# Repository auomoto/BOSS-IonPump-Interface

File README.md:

# BOSS-IonPump-Interface
The BOSS CCD dewars use a Modion C-1765V 2l/s ion pump with a custom vacuum fitting. This model number is not on the current modionvacuum.com website but the C-1765M looks similar.
The power supply is a Modion C-1766Q, which supplies the high voltage and also presents an analog signal indicating internal current that can be used as a vacuum pressure measurement. This power supply has an unusual 5-pin connector with a wall plug-in supply to supply power and also break out the signals.
To distribute the signals to the BOSS motion controller system (specMech) we use an interface box that supplies isolated 15 V to the two ion pumps (one on each of the two dewars) and conditions the analog signal for transmission to the control system.
[Link to the interface board description](https://docs.google.com/document/d/1ESppHA3kPF6aFfvCehlsRecCQ0mpgMWIIbT9OZ6ddFA/edit#)

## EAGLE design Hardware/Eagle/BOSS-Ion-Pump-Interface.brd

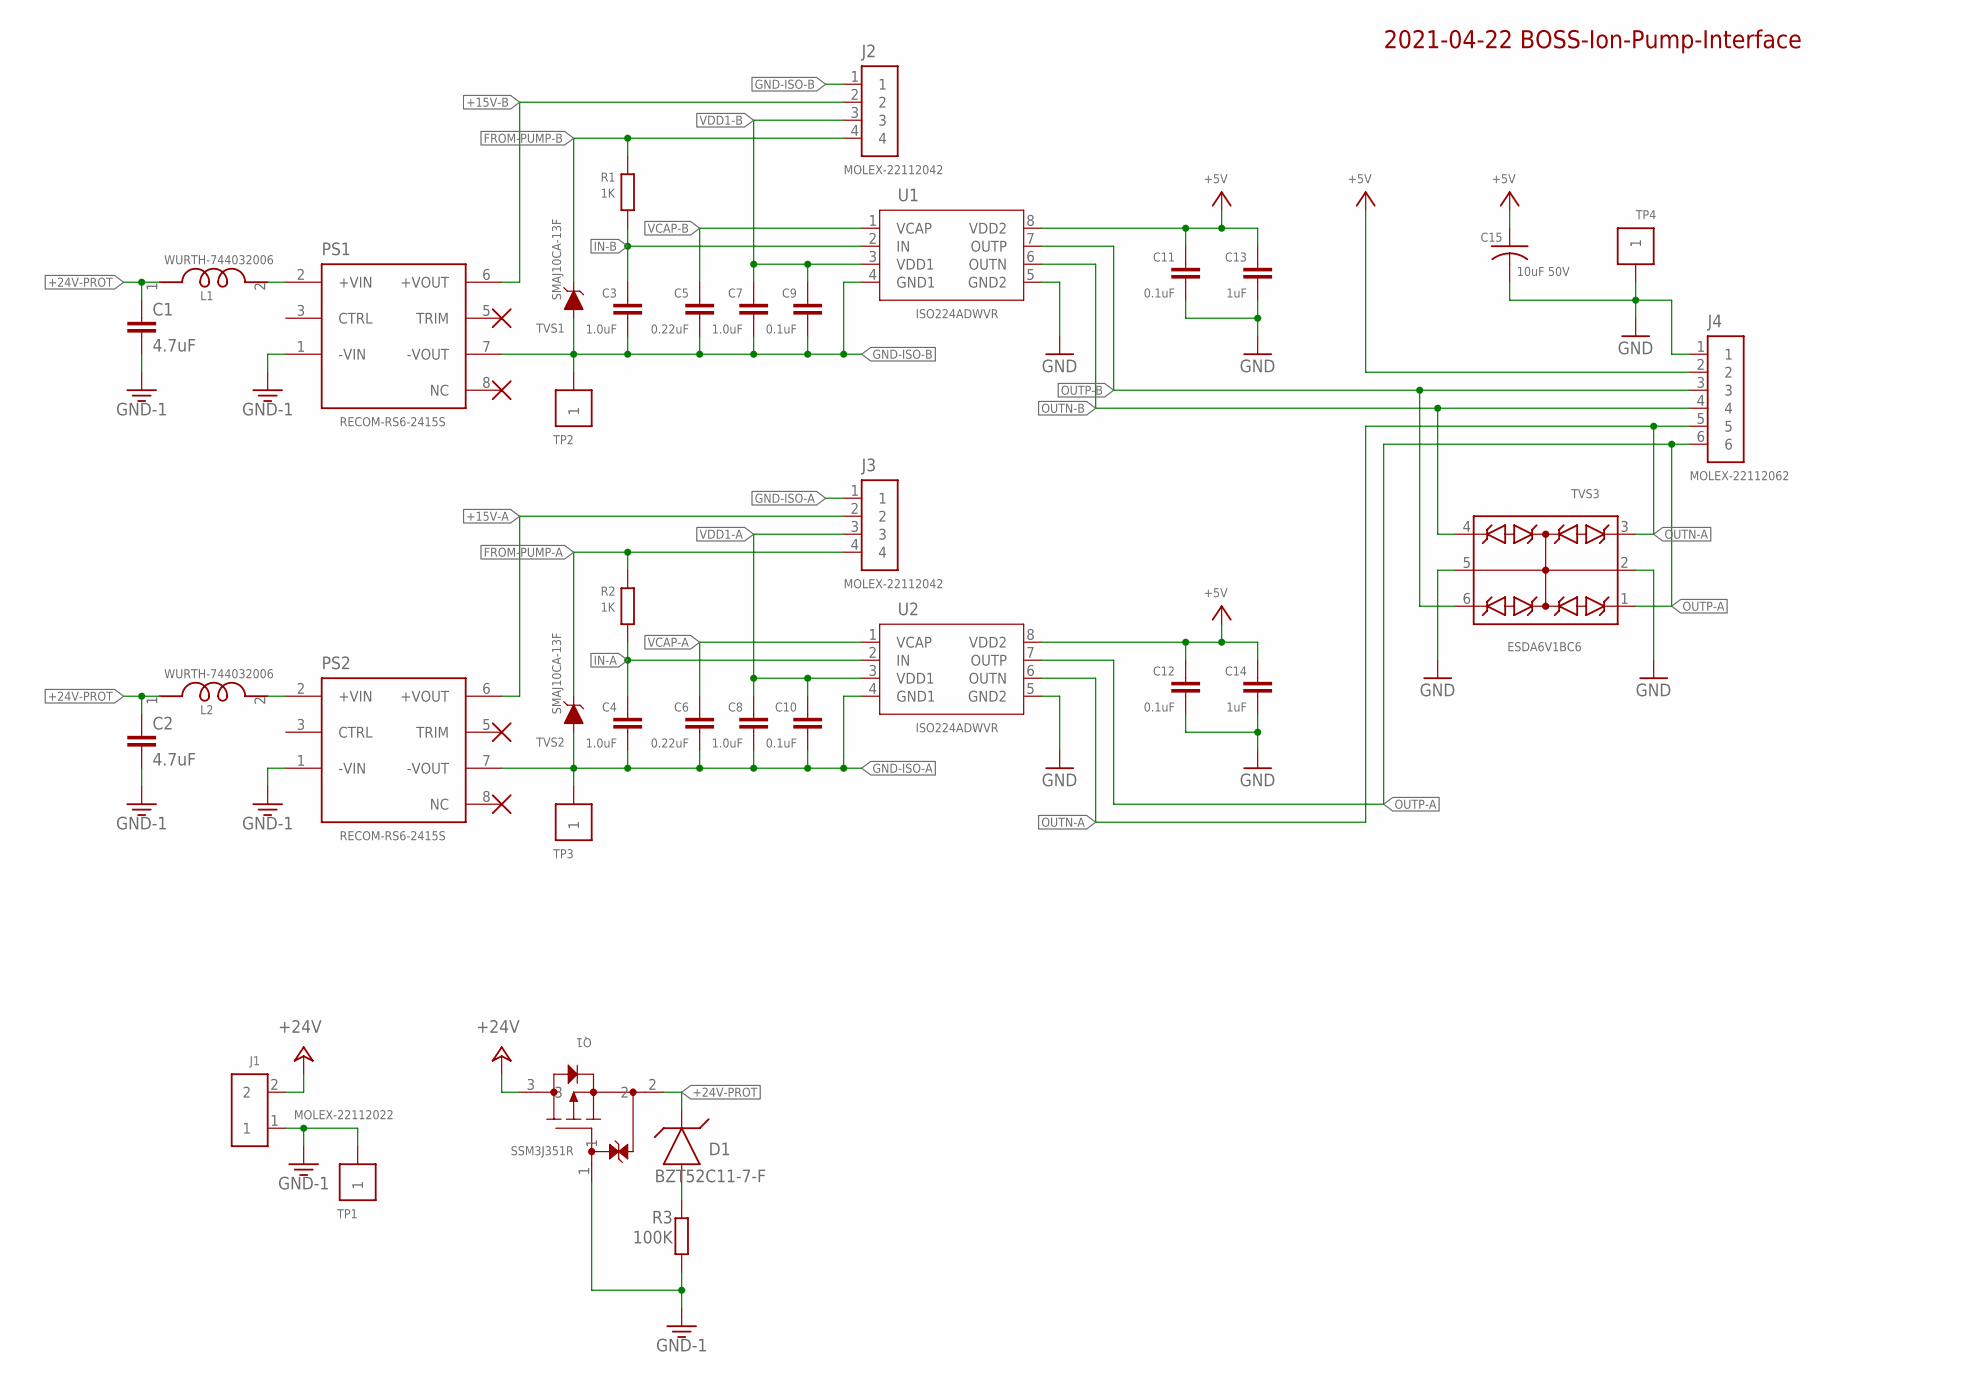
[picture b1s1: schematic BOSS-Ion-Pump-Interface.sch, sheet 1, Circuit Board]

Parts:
C1, C2: 4.7uF; C1206
C3, C4: 1.0uF; C0805
C5, C6: 0.22uF; C1206
C7, C8: 1.0uF; C1206
C9, C10: 0.1uF; C1206
C11, C12: 0.1uF; C0805
C13, C14: 1uF; C0805
C15: 10uF 50V; C1210
D1: BZT52C11-7-F; SOD123_DIO
J1: MOLEX-22112022; 1X02-MOLEX-22112022
J2, J3: MOLEX-22112042; 1X04-MOLEX-22112042
J4: MOLEX-22112062; 1X06-MOLEX-22112062
L1, L2: WURTH-744032006; WURTH-1210-INDUCTOR
PS1, PS2: RECOM-RS6-2415S; CONV_RS6-2415S
Q1: SSM3J351R; SOT-23F_TOS
R1, R2: 1K; R0805
R3: 100K; R0805
TP1, TP2, TP3, TP4: TP5000-TESTPOINT-BLK
TVS1, TVS2: SMAJ10CA-13F; SMA_DIO-M
TVS3: ESDA6V1BC6; SOT95P280X145-6N
U1, U2: ISO224ADWVR; DWV8_TEX

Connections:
+5V: C11.1, C12.1, C13.1, C14.1, C15.1, J4.2, U1.8 (VDD2), U2.8 (VDD2)
+15V-A: J3.2, PS2.6 (+VOUT)
+15V-B: J2.2, PS1.6 (+VOUT)
+24V: J1.2, Q1.3
+24V-PROT: C1.1, C2.1, D1.1 (C), L1.1, L2.1, Q1.2
+VIN-A: L2.2, PS2.2 (+VIN)
+VIN-B: L1.2, PS1.2 (+VIN)
FROM-PUMP-A: J3.4, R2.1, TVS2.1 (C)
FROM-PUMP-B: J2.4, R1.1, TVS1.1 (C)
GND: C11.2, C12.2, C13.2, C14.2, C15.2, J4.1, TP4.P$1, TVS3.2 (CC1), TVS3.5 (CC2), U1.5 (GND2), U2.5 (GND2)
GND-1: C1.2, C2.2, J1.1, PS1.1 (-VIN), PS2.1 (-VIN), Q1.1, R3.1, TP1.P$1
GND-ISO-A: C4.2, C6.2, C8.2, C10.2, J3.1, PS2.7 (-VOUT), TP3.P$1, TVS2.2 (A), U2.4 (GND1)
GND-ISO-B: C3.2, C5.2, C7.2, C9.2, J2.1, PS1.7 (-VOUT), TP2.P$1, TVS1.2 (A), U1.4 (GND1)
IN-A: C4.1, R2.2, U2.2 (IN)
IN-B: C3.1, R1.2, U1.2 (IN)
OUTN-A: J4.5, TVS3.3 (C2), U2.6 (OUTN)
OUTN-B: J4.4, TVS3.4 (C3), U1.6 (OUTN)
OUTP-A: J4.6, TVS3.1 (C1), U2.7 (OUTP)
OUTP-B: J4.3, TVS3.6 (C4), U1.7 (OUTP)
REVERSE-POL-ZENER: D1.2 (A), R3.2
VCAP-A: C6.1, U2.1 (VCAP)
VCAP-B: C5.1, U1.1 (VCAP)
VDD1-A: C8.1, C10.1, J3.3, U2.3 (VDD1)
VDD1-B: C7.1, C9.1, J2.3, U1.3 (VDD1)

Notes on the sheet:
2021-04-22 BOSS-Ion-Pump-Interface

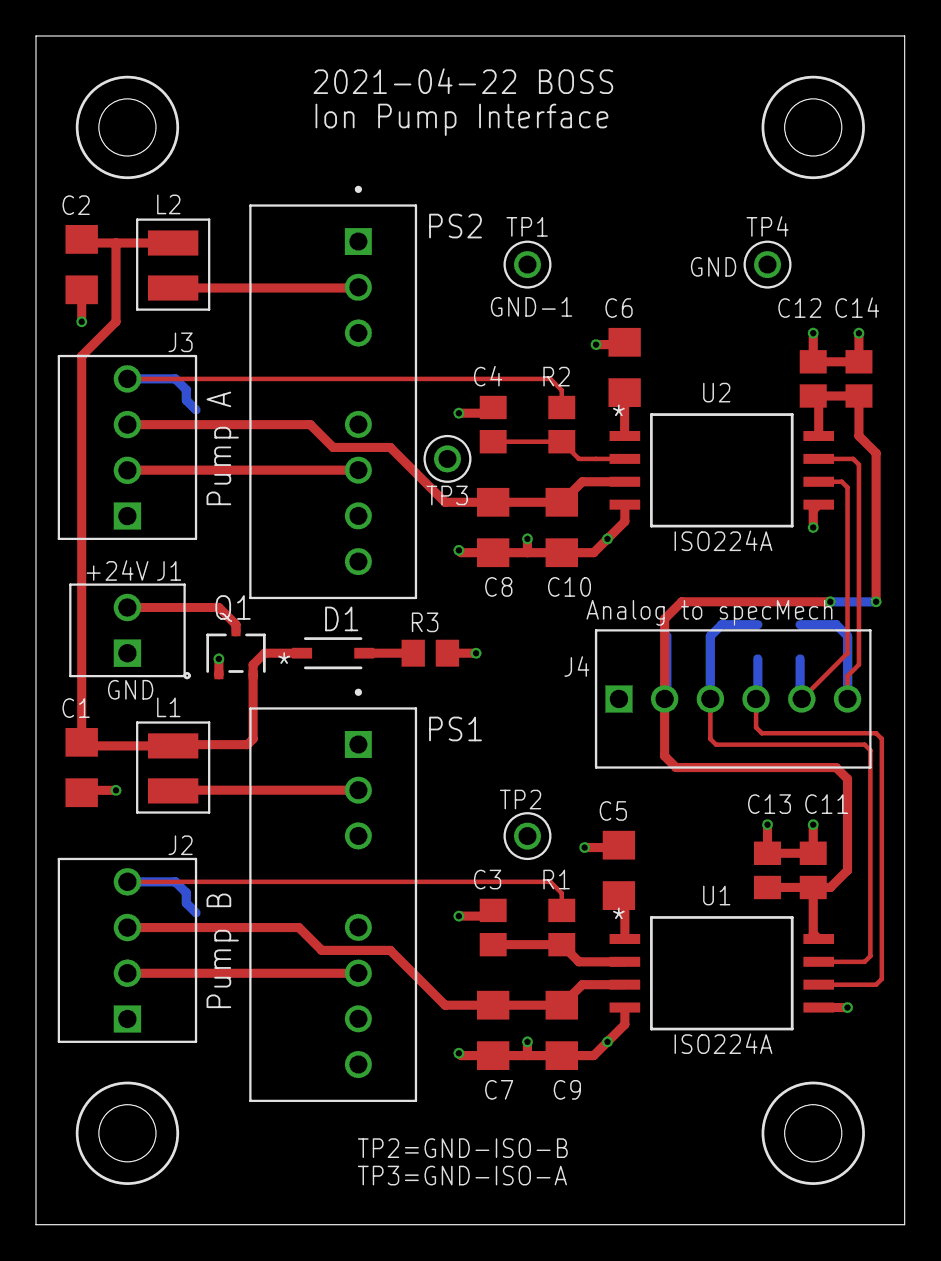
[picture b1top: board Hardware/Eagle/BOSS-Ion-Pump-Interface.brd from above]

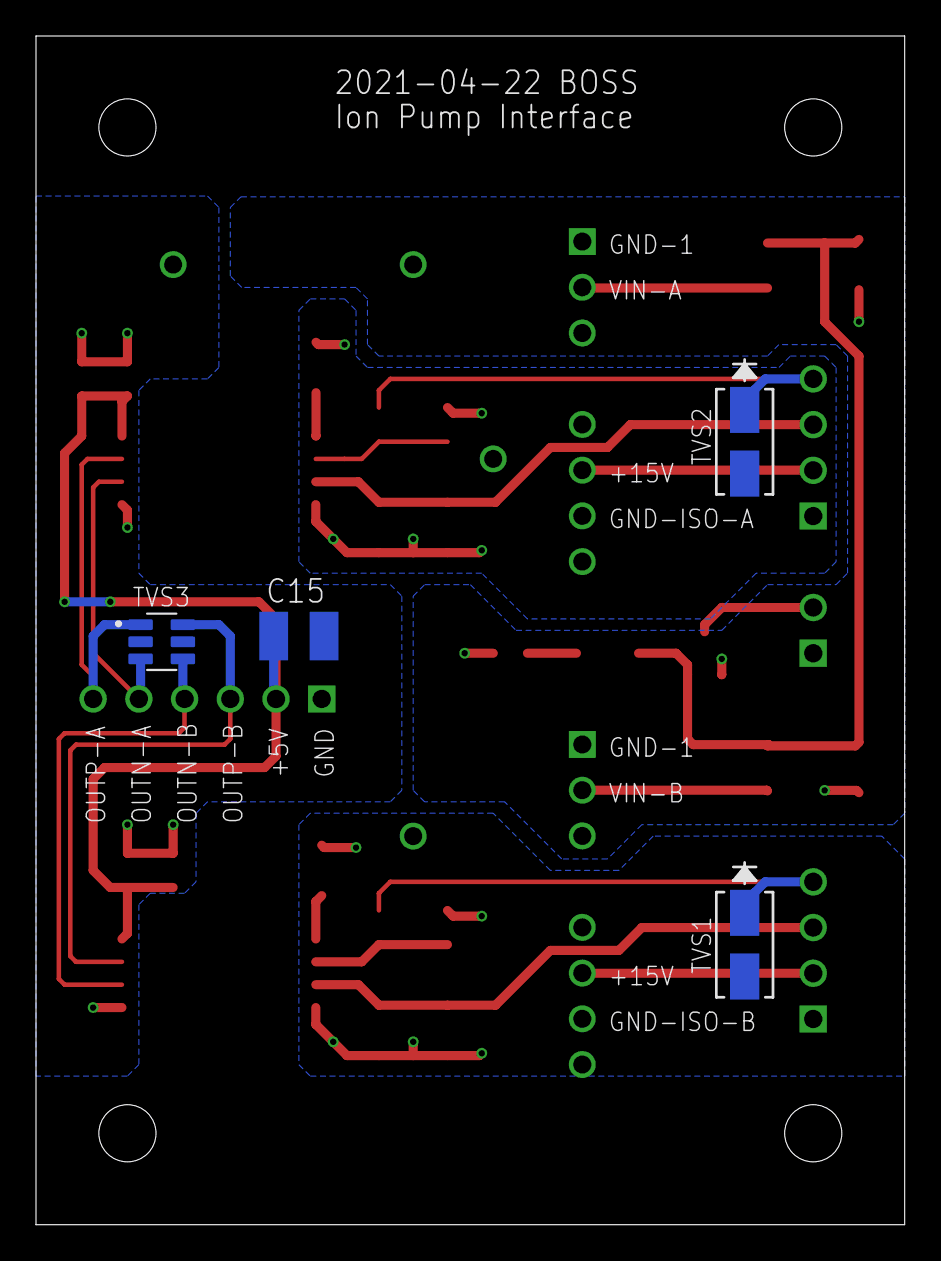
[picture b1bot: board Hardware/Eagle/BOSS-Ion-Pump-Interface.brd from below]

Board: 2 copper layers, 48.3 x 66.0 mm, 37 parts (4 on the bottom side), 24 nets.

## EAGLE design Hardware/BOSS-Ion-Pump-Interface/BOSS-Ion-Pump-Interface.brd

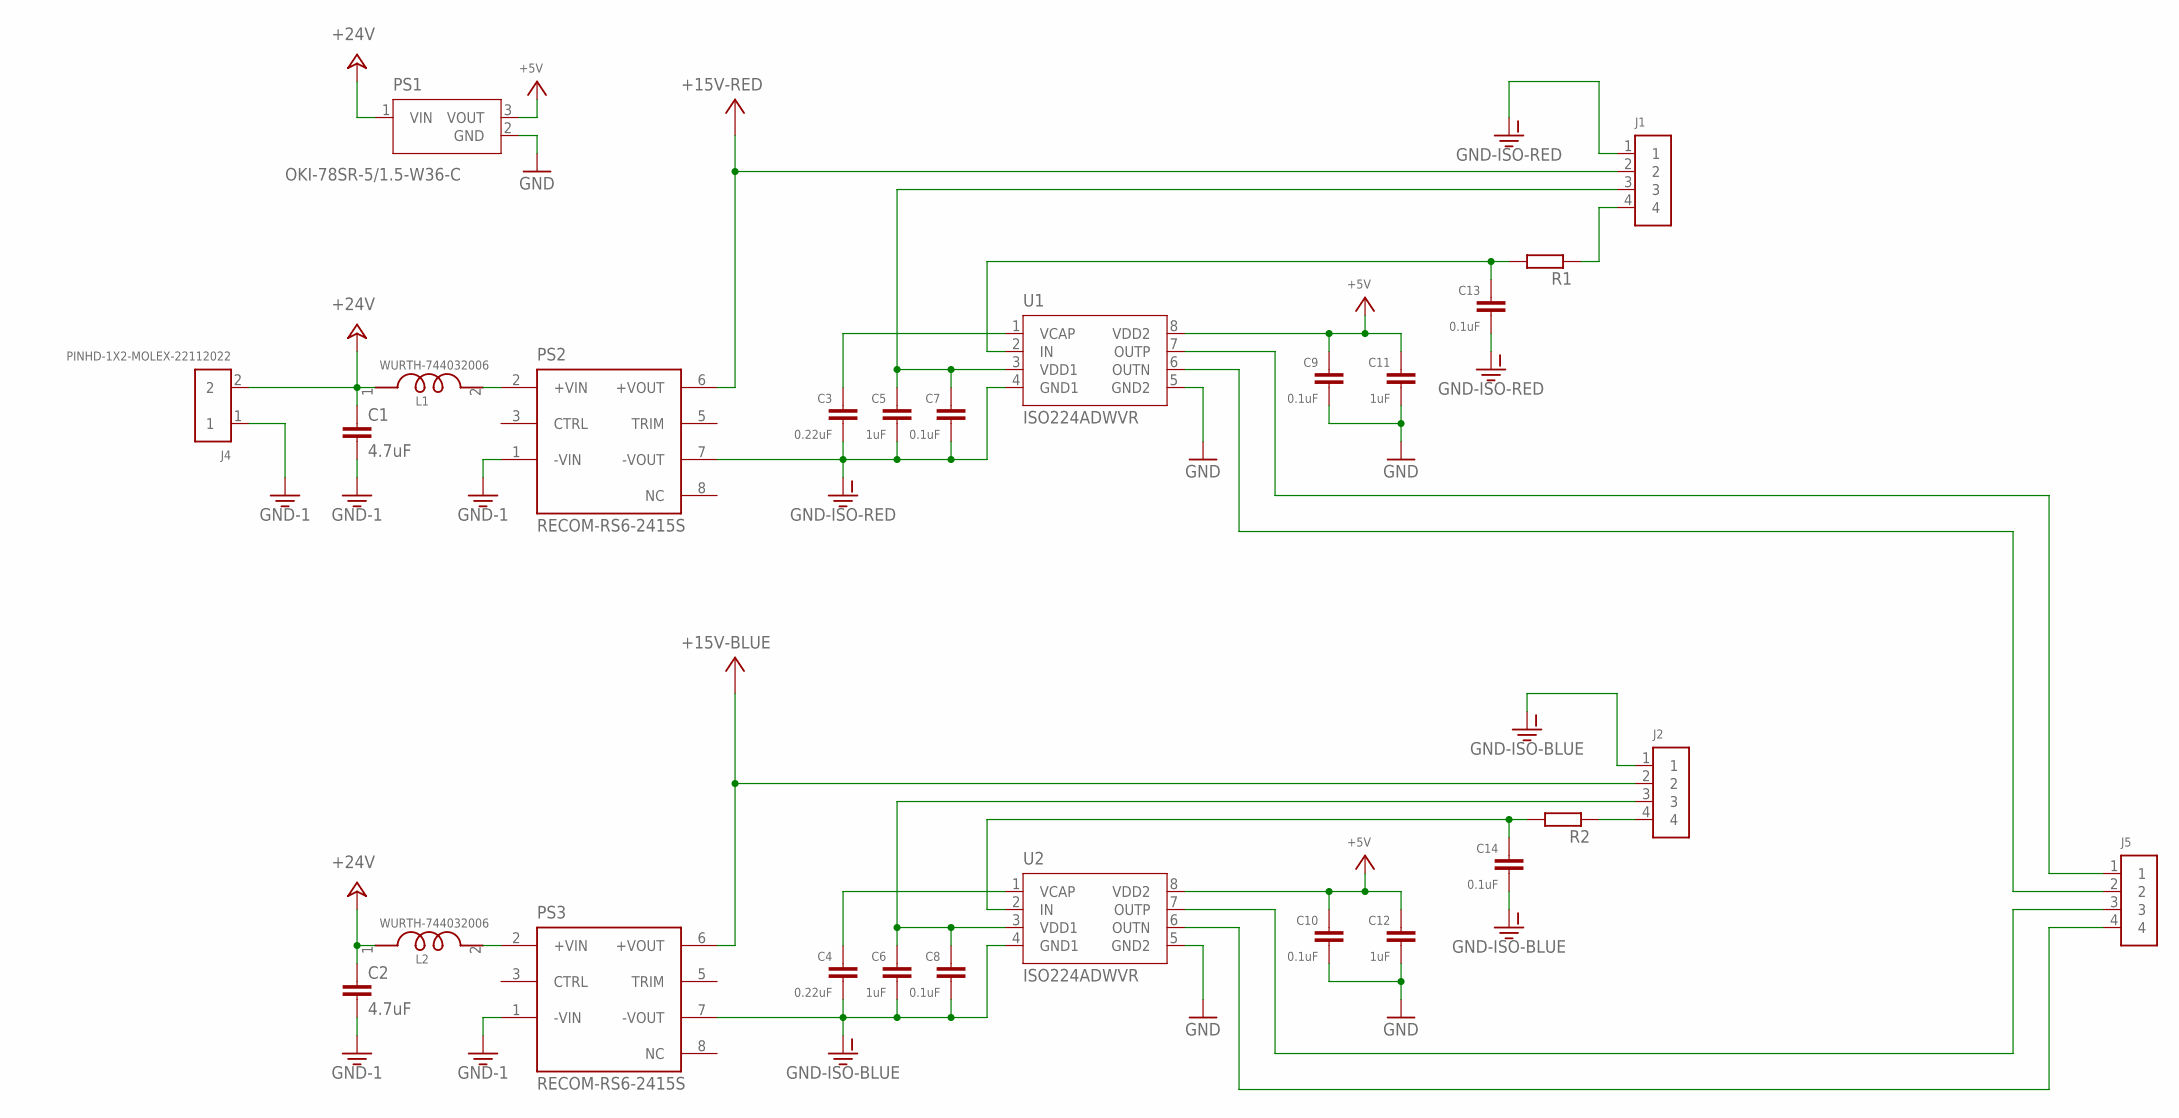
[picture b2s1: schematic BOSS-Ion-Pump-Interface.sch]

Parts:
C1, C2: 4.7uF; C1206
C3, C4: 0.22uF; C0805
C5, C6, C11, C12: 1uF; C0805
C7, C8, C9, C10, C13, C14: 0.1uF; C0805
J1, J2, J5: PINHD-1X4-MOLEX-22112042; 1X04-MOLEX-22112042
J4: PINHD-1X2-MOLEX-22112022; 1X02-MOLEX-22112022
L1, L2: WURTH-744032006; WURTH-1210-INDUCTOR
PS1: OKI-78SR-5/1.5-W36-C; CONV_OKI-78SR-5/1.5-W36-C
PS2, PS3: RECOM-RS6-2415S; CONV_RS6-2415S
R1, R2: R-EU_R0805; R0805
U1, U2: ISO224ADWVR; DWV8_TEX

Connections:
+5V: C9.1, C10.1, C11.1, C12.1, PS1.3 (VOUT), U1.8 (VDD2), U2.8 (VDD2)
+15V-BLUE: J2.2, PS3.6 (+VOUT)
+15V-RED: J1.2, PS2.6 (+VOUT)
+24V: C1.1, C2.1, J4.2, L1.1, L2.1, PS1.1 (VIN)
BLUE+: J5.3, U2.7 (OUTP)
BLUE-: J5.4, U2.6 (OUTN)
GND: C9.2, C10.2, C11.2, C12.2, PS1.2 (GND), U1.5 (GND2), U2.5 (GND2)
GND-1: C1.2, C2.2, J4.1, PS2.1 (-VIN), PS3.1 (-VIN)
GND-ISO-1: C3.2, C5.2, C7.2, C13.2, J1.1, PS2.7 (-VOUT), U1.4 (GND1)
GND-ISO-2: C4.2, C6.2, C8.2, C14.2, J2.1, PS3.7 (-VOUT), U2.4 (GND1)
IN-BLUE: C14.1, R2.2, U2.2 (IN)
IN-RED: C13.1, R1.2, U1.2 (IN)
unnamed: C3.1, U1.1 (VCAP)
unnamed: L1.2, PS2.2 (+VIN)
unnamed: J1.4, R1.1
unnamed: C4.1, U2.1 (VCAP)
unnamed: L2.2, PS3.2 (+VIN)
unnamed: J2.4, R2.1
RED+: J5.1, U1.7 (OUTP)
RED-: J5.2, U1.6 (OUTN)
VDD1-BLUE: C6.1, C8.1, J2.3, U2.3 (VDD1)
VDD1-RED: C5.1, C7.1, J1.3, U1.3 (VDD1)

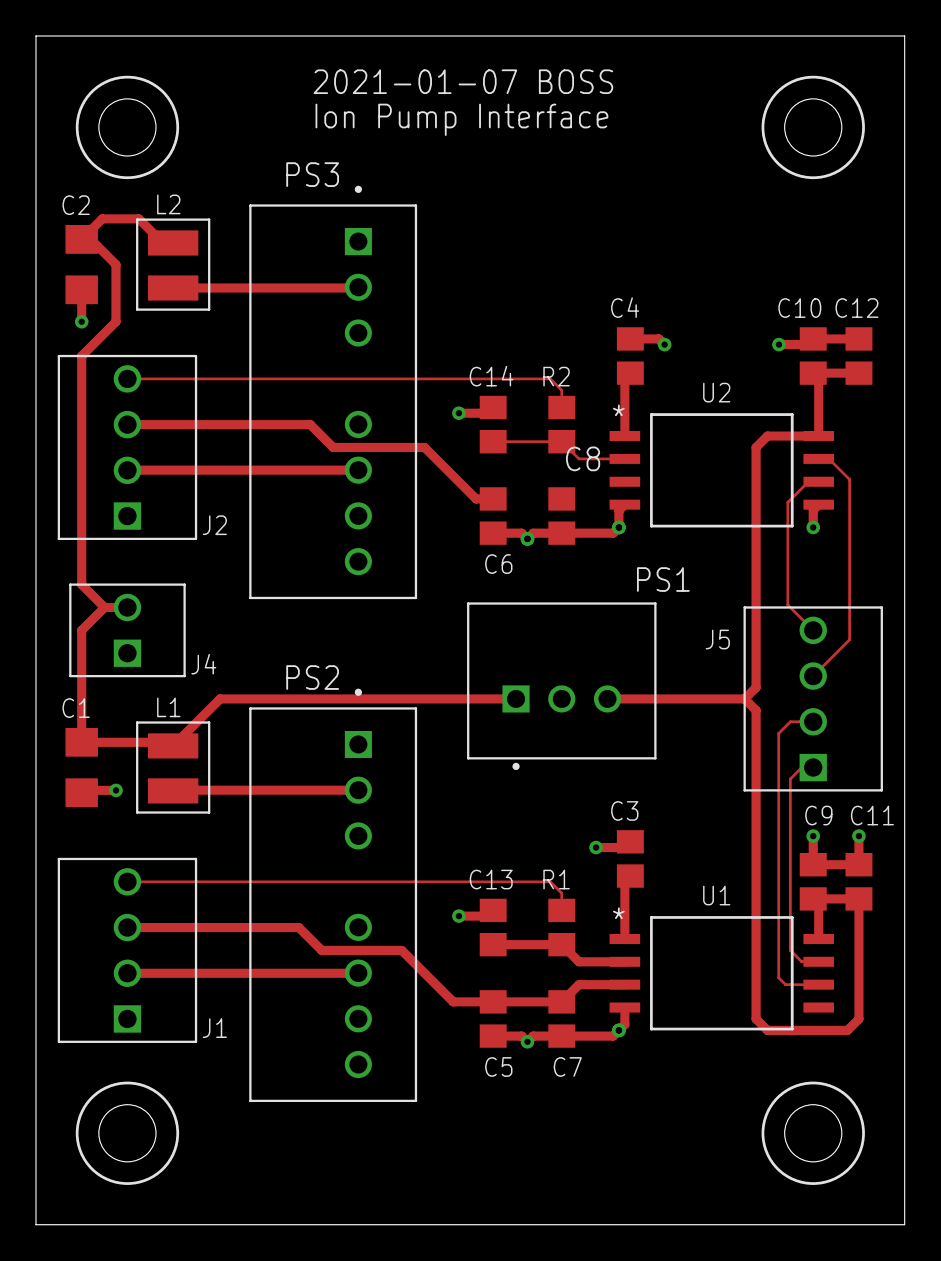
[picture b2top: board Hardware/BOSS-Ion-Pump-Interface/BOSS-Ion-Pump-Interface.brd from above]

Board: 2 copper layers, 48.3 x 66.0 mm, 27 parts (0 on the bottom side), 22 nets.

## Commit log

2021-01-08 2021-01-07 version
    To do: Remove the 5V supply and get it from specMech
2021-01-10 Increased capacitor voltages and changed to 1206
2021-01-12 Added test points, cleaned up ERC check
2021-01-13 Added external parts (switches and panel connectors)
2021-01-13 Printed new schematic
2021-01-15 Minor edits for upload to Fusion 360
2021-01-21 Measured some dimensions; no circut or layout changes
2021-01-24 Removed Eagle backups for gitignore
2021-01-27 Re-labeled nets, added 10uF filter on+5V in
2021-01-27 minor re-routing
2021-01-28 Added reverse polarity protection
2021-02-02 Changed TVS diode to 10 V from 6 V and labeled reverse polarity Zener
2021-02-04 Exported Hammond box machining drawing and STEP files
2021-02-20 Added names to the reverse polarity zener net
2021-02-23 Changed the incorrect label on the output amp to ISO224A
2021-05-20 Added wire colors to connectors
2021-05-27 Minor edits to schematic
2021-07-24 Production version

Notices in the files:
parts and their libraries:
COPYRIGHT: Copyright (C) 2018 Accelerated Designs. All rights reserved
